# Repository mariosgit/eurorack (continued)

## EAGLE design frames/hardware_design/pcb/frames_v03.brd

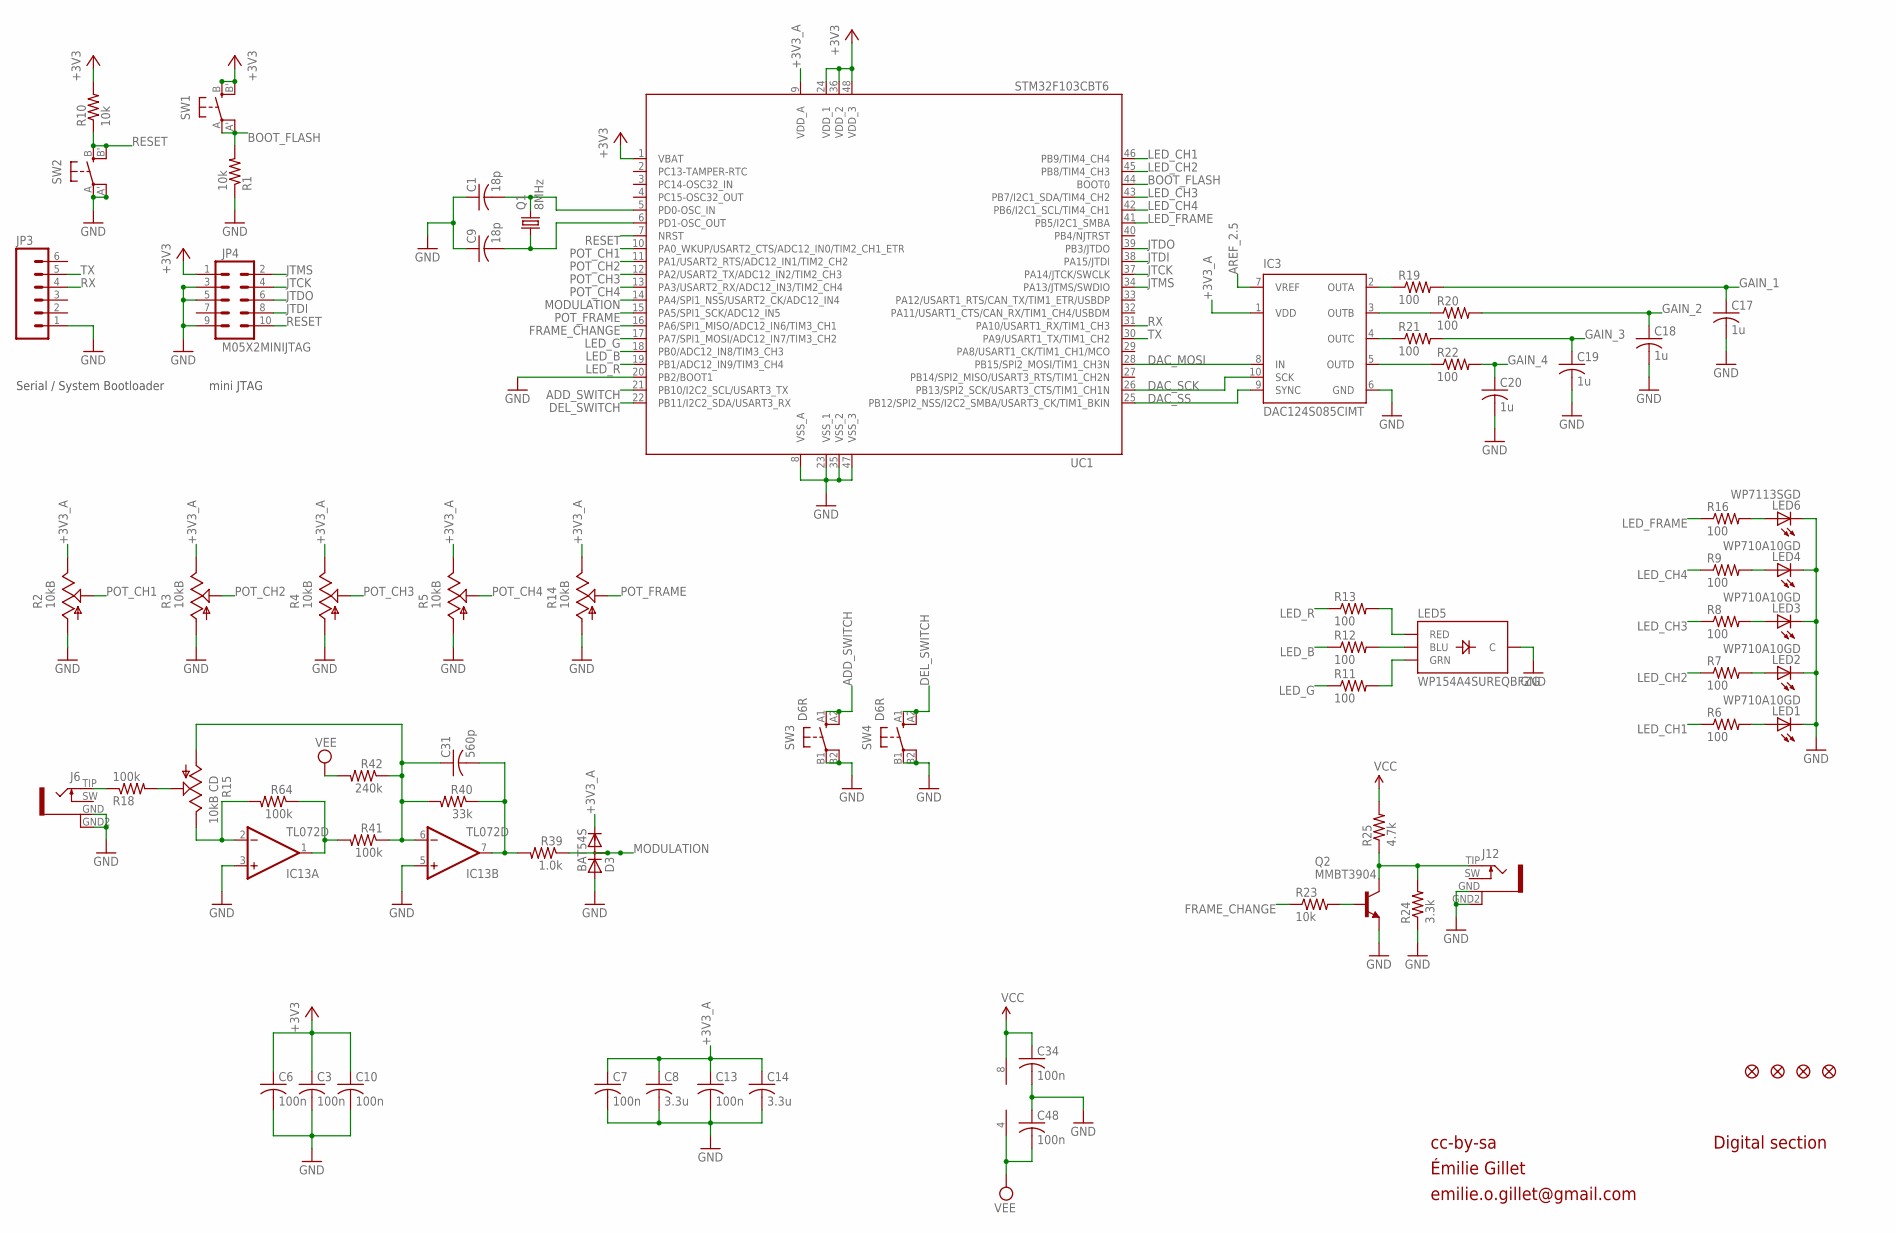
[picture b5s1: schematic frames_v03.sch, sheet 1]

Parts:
C1, C9: 18p; C0603
C3, C6, C7, C10, C13, C34, C48: 100n; C0603
C8, C14: 3.3u; C0603
C17, C18, C19, C20: 1u; C0603
C31: 560p; C0603
D3: BAT54S; SOT23
F1, F2, F3, F4: FIDUCIAL1X2; FIDUCIAL-1X2
IC3: DAC124S085CIMT; MSOP10
IC13: TL072D; SO08
J6, J12: PJ301WQP; WQP_PJ_301BM
JP3: M06SIP; 1X06
JP4: M05X2MINIJTAG; 2X5-1.27
LED1, LED2, LED3, LED4: WP710A10GD; LED3MM
LED5: WP154A4SUREQBFZG; LED-TRICOLOR-THROUGHHOLE
LED6: WP7113SGD; LED5MM
Q1: 8MHz; HC49UP
Q2: MMBT3904; SOT23-BEC
R1, R10, R23: 10k; R0603
R2, R3, R4, R5, R14: 10kB; ALPS_POT_VERTICAL_PS
R6, R7, R8, R9, R11, R12, R13, R16, R19, R20, R21, R22: 100; R0603
R15: 10kB CD; ALPS_POT_VERTICAL_PS
R18, R41, R64: 100k; R0603
R24: 3.3k; R0603
R25: 4.7k; R0603
R39: 1.0k; R0603
R40: 33k; R0603
R42: 240k; R0603
SW1, SW2: EVQQ2; EVQ-Q2
SW3, SW4: D6R
UC1: STM32F103CBT6; LQFP48

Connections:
+3V3: C3.1, C6.1, C10.1, JP4.1, R10.2, SW1.B (S), SW1.B' (S1), UC1.1 (VBAT), UC1.24 (VDD_1), UC1.36 (VDD_2), UC1.48 (VDD_3); also elsewhere on the board
+3V3_A: C7.1, C8.1, C13.1, C14.1, D3.2 (C), IC3.1 (VDD), R2.P$1 (E), R3.P$1 (E), R4.P$1 (E), R5.P$1 (E), R14.P$1 (E), UC1.9 (VDD_A); also elsewhere on the board
ADD_SWITCH: SW3.A1 (S), SW3.A2 (S1), UC1.21 (PB10/I2C2_SCL/USART3_TX)
AREF_2.5: IC3.7 (VREF); also elsewhere on the board
BOOT_FLASH: R1.2, SW1.A, SW1.A' (P1), UC1.44 (BOOT0)
DAC_MOSI: IC3.8 (IN), UC1.28 (PB15/SPI2_MOSI/TIM1_CH3N)
DAC_SCK: IC3.10 (SCK), UC1.26 (PB13/SPI2_SCK/USART3_CTS/TIM1_CH1N)
DAC_SS: IC3.9 (SYNC), UC1.25 (PB12/SPI2_NSS/I2C2_SMBA/USART3_CK/TIM1_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)
DEL_SWITCH: SW4.A1 (S), SW4.A2 (S1), UC1.22 (PB11/I2C2_SDA/USART3_RX)
FRAME_CHANGE: R23.1, UC1.16 (PA6/SPI1_MISO/ADC12_IN6/TIM3_CH1)
GAIN_1: C17.1, R19.2; also elsewhere on the board
GAIN_2: C18.1, R20.2; also elsewhere on the board
GAIN_3: C19.1, R21.2; also elsewhere on the board
GAIN_4: C20.1, R22.2; also elsewhere on the board
GATE2_LED: LED3.A, R8.2
GATE3_LED: LED2.A, R7.2
GATE4_LED: LED1.A, R6.2
GND: C1.1, C3.2, C6.2, C7.2, C8.2, C9.1, C10.2, C13.2, C14.2, C17.2, C18.2, C19.2, C20.2, C34.2, C48.1, D3.1 (A), IC3.6 (GND), IC13.3 (+IN), IC13.5 (+IN), J6.GND (1), J6.GND2 (4), J12.GND (1), J12.GND2 (4), JP3.1, JP4.3, JP4.5, JP4.9, LED1.K (C), LED2.K (C), LED3.K (C), LED4.K (C), LED5.GND (C), LED6.K (C), Q2.E, R1.1, R2.P$3 (A), R3.P$3 (A), R4.P$3 (A), R5.P$3 (A), R14.P$3 (A), R24.1, SW2.A, SW2.A' (P1), SW3.B1, SW3.B2 (P1), SW4.B1, SW4.B2 (P1), UC1.8 (VSS_A), UC1.20 (PB2/BOOT1), UC1.23 (VSS_1), UC1.35 (VSS_2), UC1.47 (VSS_3); also elsewhere on the board
JTCK: JP4.4, UC1.37 (PA14/JTCK/SWCLK)
JTDI: JP4.8, UC1.38 (PA15/JTDI)
JTDO: JP4.6, UC1.39 (PB3/JTDO)
JTMS: JP4.2, UC1.34 (PA13/JTMS/SWDIO)
LED_B: R12.1, UC1.18 (PB0/ADC12_IN8/TIM3_CH3)
LED_CH1: R6.1, UC1.46 (PB9/TIM4_CH4)
LED_CH2: R7.1, UC1.45 (PB8/TIM4_CH3)
LED_CH3: R8.1, UC1.43 (PB7/I2C1_SDA/TIM4_CH2)
LED_CH4: R9.1, UC1.42 (PB6/I2C1_SCL/TIM4_CH1)
LED_FRAME: R16.1, UC1.41 (PB5/I2C1_SMBA)
LED_G: R11.1, UC1.17 (PA7/SPI1_MOSI/ADC12_IN7/TIM3_CH2)
LED_R: R13.1, UC1.19 (PB1/ADC12_IN9/TIM3_CH4)
MODULATION: D3.3 (AC), R39.1, UC1.14 (PA4/SPI1_NSS/USART2_CK/ADC12_IN4)
unnamed: IC13.2 (-IN), R15.P$1 (E), R64.2
unnamed: R15.P$2 (S), R18.2
unnamed: LED4.A, R9.2
unnamed: C1.2, Q1.2, UC1.5 (PD0-OSC_IN)
unnamed: C9.2, Q1.1, UC1.6 (PD1-OSC_OUT)
unnamed: IC13.1 (OUT), R41.2, R64.1
unnamed: J6.TIP (2), R18.1
unnamed: C31.2, IC13.7 (OUT), R39.2, R40.1
unnamed: C31.1, IC13.6 (-IN), R15.P$3 (A), R40.2, R41.1, R42.1
unnamed: LED6.A, R16.2
unnamed: LED5.RED, R13.2
unnamed: LED5.BLU, R12.2
unnamed: LED5.GRN, R11.2
unnamed: IC3.2 (OUTA), R19.1
unnamed: IC3.3 (OUTB), R20.1
unnamed: IC3.4 (OUTC), R21.1
unnamed: J12.TIP (2), Q2.C, R24.2, R25.1
unnamed: IC3.5 (OUTD), R22.1
unnamed: Q2.B, R23.2
POT_CH1: R2.P$2 (S), UC1.10 (PA0_WKUP/USART2_CTS/ADC12_IN0/TIM2_CH1_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)
POT_CH2: R3.P$2 (S), UC1.11 (PA1/USART2_RTS/ADC12_IN1/TIM2_CH2)
POT_CH3: R4.P$2 (S), UC1.12 (PA2/USART2_TX/ADC12_IN2/TIM2_CH3)
POT_CH4: R5.P$2 (S), UC1.13 (PA3/USART2_RX/ADC12_IN3/TIM2_CH4)
POT_FRAME: R14.P$2 (S), UC1.15 (PA5/SPI1_SCK/ADC12_IN5)
RESET: JP4.10, R10.1, SW2.B (S), SW2.B' (S1), UC1.7 (NRST)
RX: JP3.4, UC1.31 (PA10/USART1_RX/TIM1_CH3)
TX: JP3.5, UC1.30 (PA9/USART1_TX/TIM1_CH2)
VCC: C34.1, IC13.8 (V+), R25.2; also elsewhere on the board
VEE: C48.2, IC13.4 (V-), R42.2; also elsewhere on the board

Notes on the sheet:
cc-by-sa
Serial / System Bootloader
mini JTAG
Digital section
Émilie Gillet
emilie.o.gillet@gmail.com

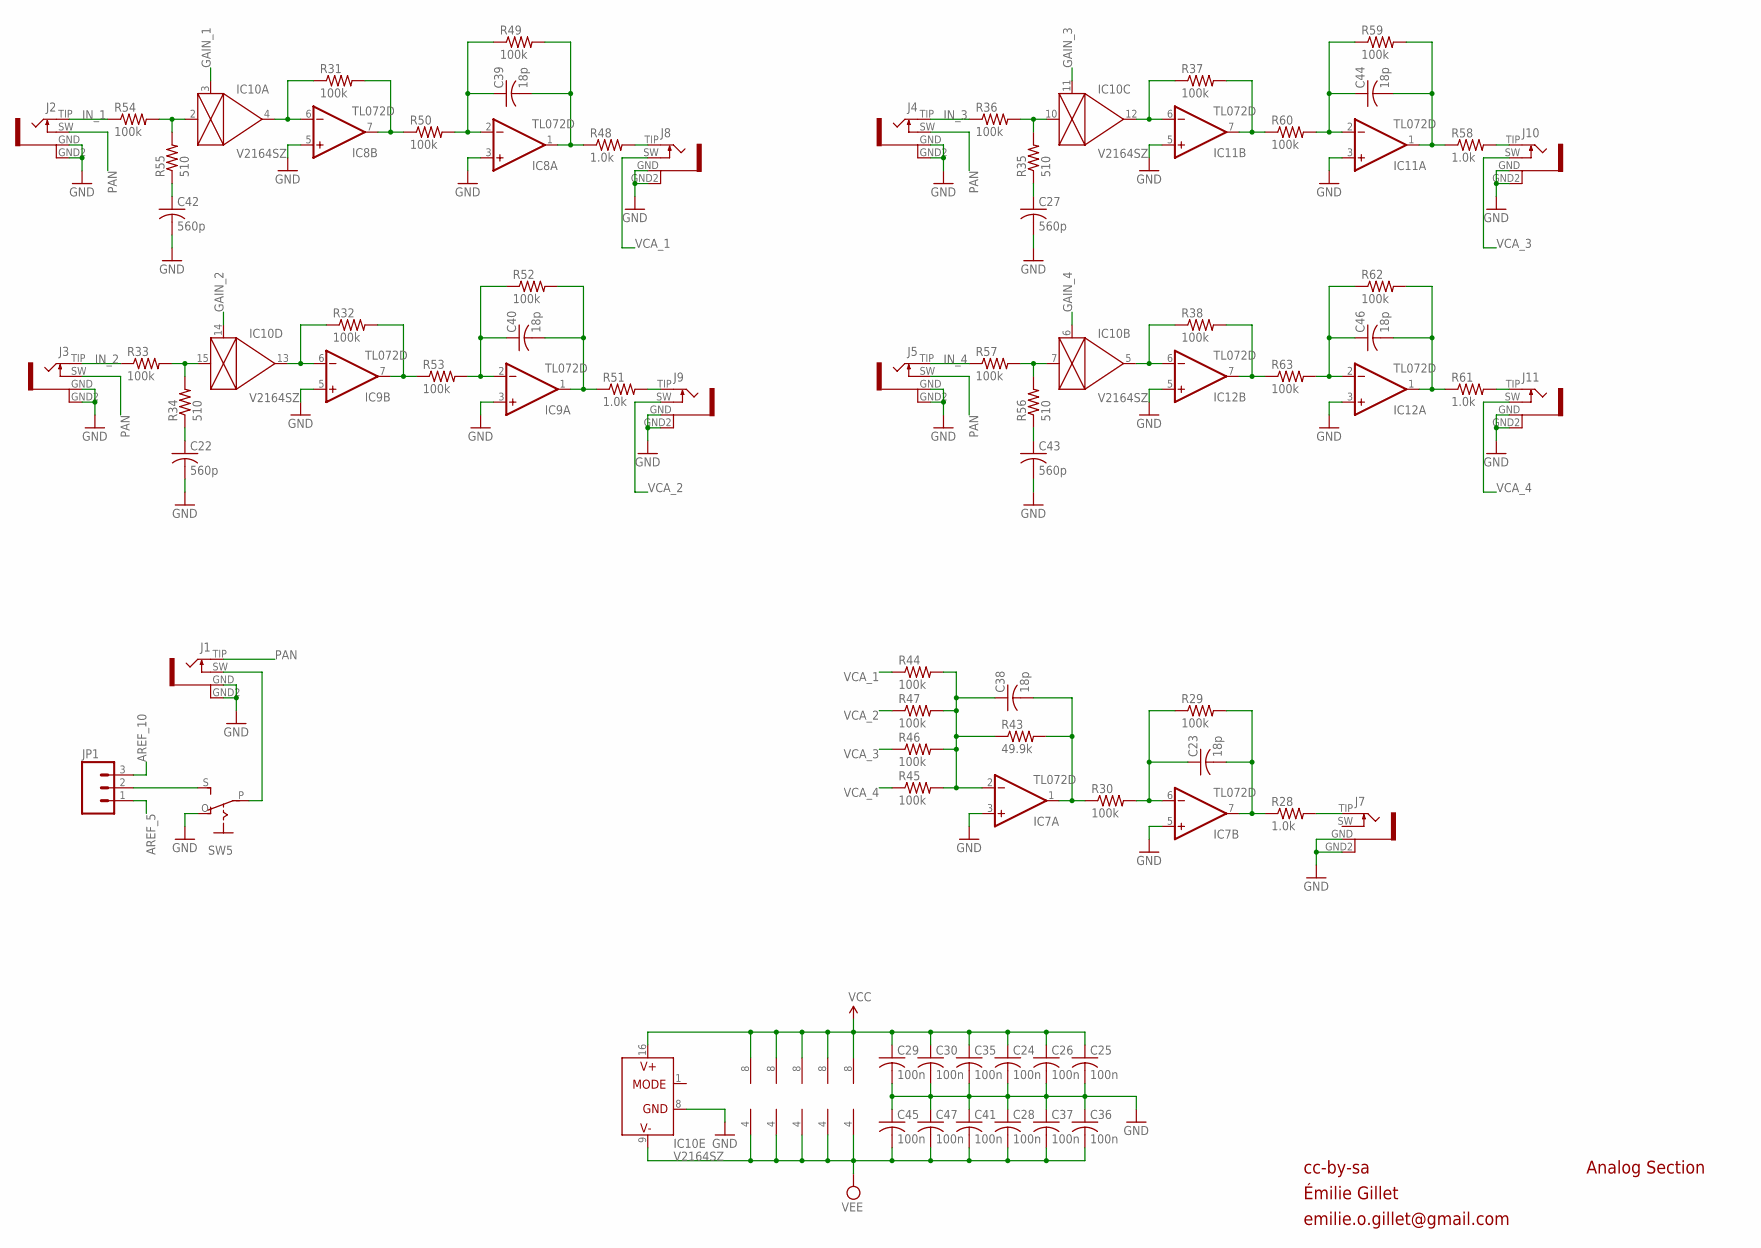
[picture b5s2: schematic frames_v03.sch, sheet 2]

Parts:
C22, C27, C42, C43: 560p; C0603
C23, C38, C39, C40, C44, C46: 18p; C0603
C24, C25, C26, C28, C29, C30, C35, C36, C37, C41, C45, C47: 100n; C0603
IC7, IC8, IC9, IC11, IC12: TL072D; SO08
IC10: V2164SZ; SOIC16N
J1, J2, J3, J4, J5, J7, J8, J9, J10, J11: PJ301WQP; WQP_PJ_301BM
JP1: M03PTH; 1X03
R28, R48, R51, R58, R61: 1.0k; R0603
R29, R30, R31, R32, R33, R36, R37, R38, R44, R45, R46, R47, R49, R50, R52, R53, R54, R57, R59, R60, R62, R63: 100k; R0603
R34, R35, R55, R56: 510; R0603
R43: 49.9k; R0603
SW5: S-ON-ONSMALL_SLIDE; ES_100SP1T6B11M2QEH_SMALL

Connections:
AREF_5: JP1.1; also elsewhere on the board
AREF_10: JP1.3; also elsewhere on the board
FB_CURRENT: IC10.2 (IN), R54.2, R55.2
FB_CURRENT1: IC10.15 (IN), R33.2, R34.2
FB_CURRENT2: IC10.10 (IN), R35.2, R36.2
FB_CURRENT3: IC10.7 (IN), R56.2, R57.2
GAIN_1: IC10.3 (CTRL); also elsewhere on the board
GAIN_2: IC10.14 (CTRL); also elsewhere on the board
GAIN_3: IC10.11 (CTRL); also elsewhere on the board
GAIN_4: IC10.6 (CTRL); also elsewhere on the board
GND: C22.2, C24.2, C25.2, C26.2, C27.2, C28.1, C29.2, C30.2, C35.2, C36.1, C37.1, C41.1, C42.2, C43.2, C45.1, C47.1, IC7.3 (+IN), IC7.5 (+IN), IC8.3 (+IN), IC8.5 (+IN), IC9.3 (+IN), IC9.5 (+IN), IC10.8 (GND), IC11.3 (+IN), IC11.5 (+IN), IC12.3 (+IN), IC12.5 (+IN), J1.GND (1), J1.GND2 (4), J2.GND (1), J2.GND2 (4), J3.GND (1), J3.GND2 (4), J4.GND (1), J4.GND2 (4), J5.GND (1), J5.GND2 (4), J7.GND (1), J7.GND2 (4), J8.GND (1), J8.GND2 (4), J9.GND (1), J9.GND2 (4), J10.GND (1), J10.GND2 (4), J11.GND (1), J11.GND2 (4), SW5.O; also elsewhere on the board
IN_1: J2.TIP (2), R54.1
IN_2: J3.TIP (2), R33.1
IN_3: J4.TIP (2), R36.1
IN_4: J5.TIP (2), R57.1
unnamed: C42.1, R55.1
unnamed: J7.TIP (2), R28.2
unnamed: IC9.7 (OUT), R32.2, R53.1
unnamed: C27.1, R35.1
unnamed: IC8.6 (-IN), IC10.4 (OUT), R31.1
unnamed: C39.1, IC8.2 (-IN), R49.1, R50.2
unnamed: C39.2, IC8.1 (OUT), R48.1, R49.2
unnamed: C23.2, IC7.7 (OUT), R28.1, R29.2
unnamed: C22.1, R34.1
unnamed: C38.1, IC7.2 (-IN), R43.1, R44.2, R45.2, R46.2, R47.2
unnamed: IC9.6 (-IN), IC10.13 (OUT), R32.1
unnamed: C23.1, IC7.6 (-IN), R29.1, R30.2
unnamed: C40.1, IC9.2 (-IN), R52.1, R53.2
unnamed: C40.2, IC9.1 (OUT), R51.1, R52.2
unnamed: IC10.12 (OUT), IC11.6 (-IN), R37.1
unnamed: C44.1, IC11.2 (-IN), R59.1, R60.2
unnamed: C44.2, IC11.1 (OUT), R58.1, R59.2
unnamed: C43.1, R56.1
unnamed: C38.2, IC7.1 (OUT), R30.1, R43.2
unnamed: IC10.5 (OUT), IC12.6 (-IN), R38.1
unnamed: C46.1, IC12.2 (-IN), R62.1, R63.2
unnamed: C46.2, IC12.1 (OUT), R61.1, R62.2
unnamed: J1.SW (3), SW5.P
unnamed: J8.TIP (2), R48.2
unnamed: JP1.2, SW5.S
unnamed: IC12.7 (OUT), R38.2, R63.1
unnamed: J9.TIP (2), R51.2
unnamed: J11.TIP (2), R61.2
unnamed: J10.TIP (2), R58.2
PAN: J1.TIP (2), J2.SW (3), J3.SW (3), J4.SW (3), J5.SW (3)
VCA0_1: IC8.7 (OUT), R31.2, R50.1
VCA0_3: IC11.7 (OUT), R37.2, R60.1
VCA_1: J8.SW (3), R44.1
VCA_2: J9.SW (3), R47.1
VCA_3: J10.SW (3), R46.1
VCA_4: J11.SW (3), R45.1
VCC: C24.1, C25.1, C26.1, C29.1, C30.1, C35.1, IC7.8 (V+), IC8.8 (V+), IC9.8 (V+), IC10.16 (V+), IC11.8 (V+), IC12.8 (V+); also elsewhere on the board
VEE: C28.2, C36.2, C37.2, C41.2, C45.2, C47.2, IC7.4 (V-), IC8.4 (V-), IC9.4 (V-), IC10.9 (V-), IC11.4 (V-), IC12.4 (V-); also elsewhere on the board

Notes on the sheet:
cc-by-sa
Analog Section
Émilie Gillet
emilie.o.gillet@gmail.com

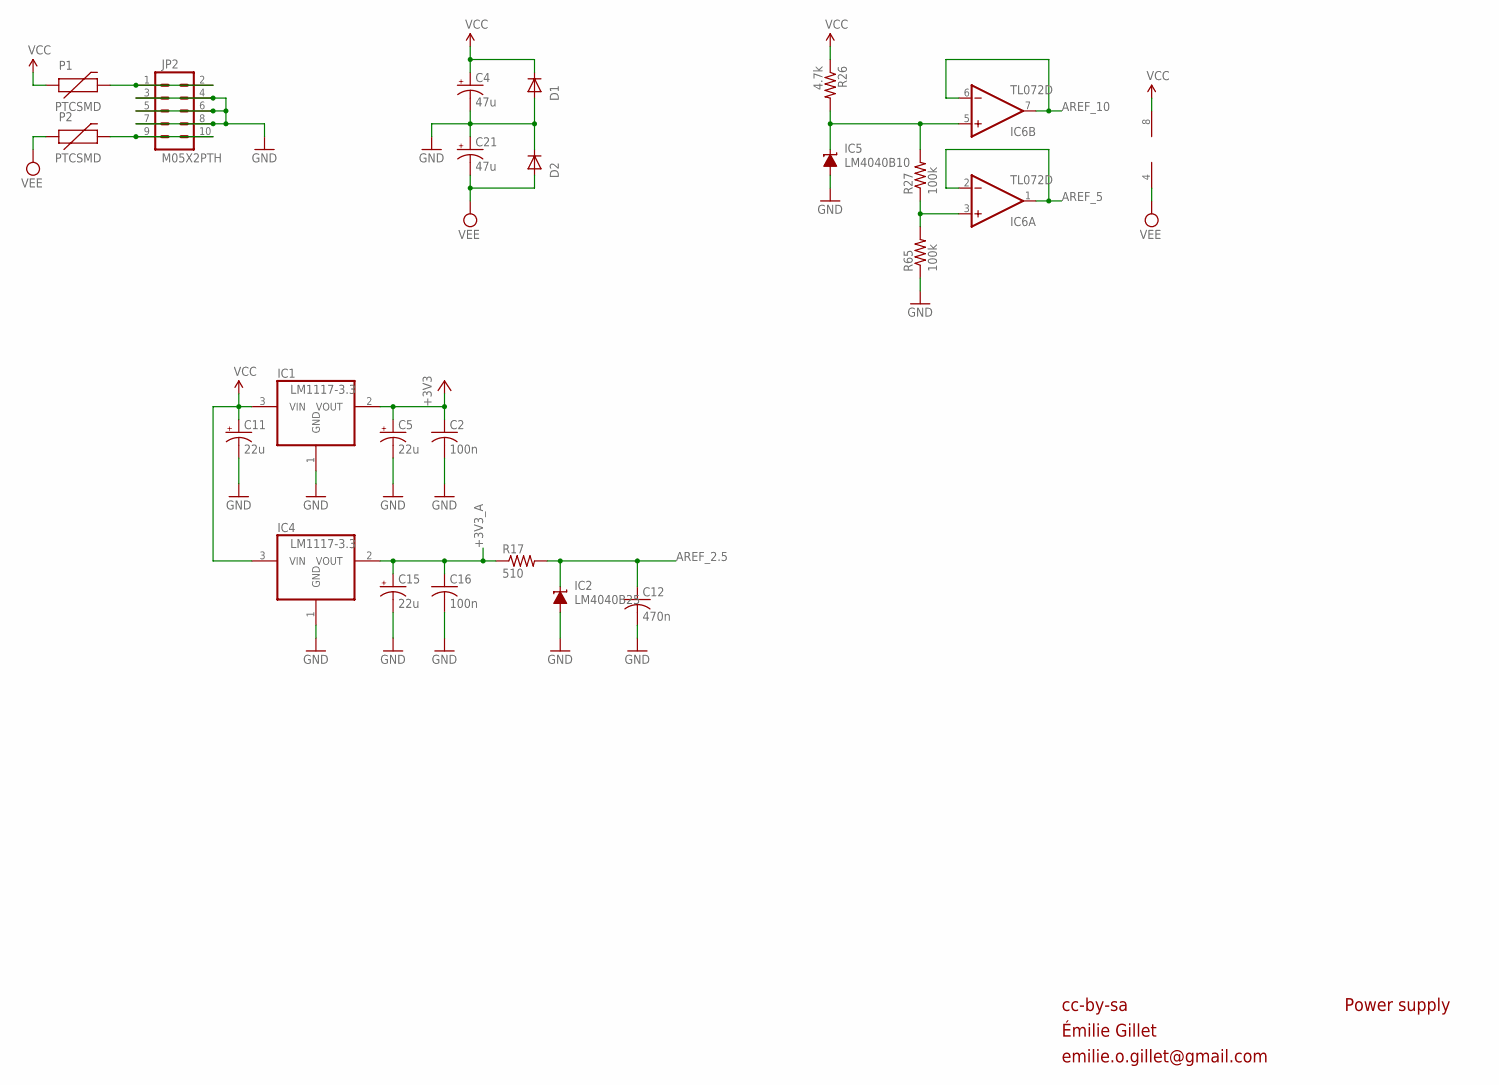
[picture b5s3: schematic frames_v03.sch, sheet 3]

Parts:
C2, C16: 100n; C0603
C4, C21: 47u; PANASONIC_D
C5, C11, C15: 22u; PANASONIC_C
C12: 470n; C0603
D1, D2: 1N5819HW; SOD123
IC1, IC4: LM1117-3.3; SOT223
IC2: LM4040B25; DBZ_R-PDSO-G3
IC5: LM4040B10; DBZ_R-PDSO-G3
IC6: TL072D; SO08
JP2: M05X2PTH; AVR_ICSP
P1, P2: PTCSMD; PTC-1206
R17: 510; R0603
R26: 4.7k; R0603
R27, R65: 100k; R0603

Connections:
+3V3: C2.1, C5.+, IC1.2 (VOUT); also elsewhere on the board
+3V3_A: C15.+, C16.1, IC4.2 (VOUT), R17.1; also elsewhere on the board
AREF_2.5: C12.1, IC2.1 (C), R17.2; also elsewhere on the board
AREF_5: IC6.1 (OUT), IC6.2 (-IN); also elsewhere on the board
AREF_10: IC6.6 (-IN), IC6.7 (OUT); also elsewhere on the board
AREF_10_0: IC5.1 (C), IC6.5 (+IN), R26.2, R27.2
GND: C2.2, C4.-, C5.-, C11.-, C12.2, C15.-, C16.2, C21.+, D1.A, D2.C, IC1.1 (GND), IC2.2 (A), IC4.1 (GND), IC5.2 (A), JP2.3, JP2.4, JP2.5, JP2.6, JP2.7, JP2.8, R65.1; also elsewhere on the board
unnamed: IC6.3 (+IN), R27.1, R65.2
unnamed: JP2.1, JP2.2, P1.2
unnamed: JP2.9, JP2.10, P2.2
VCC: C4.+, C11.+, D1.C, IC1.3 (VIN), IC4.3 (VIN), IC6.8 (V+), P1.1, R26.1; also elsewhere on the board
VEE: C21.-, D2.A, IC6.4 (V-), P2.1; also elsewhere on the board

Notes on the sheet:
cc-by-sa
Power supply
Émilie Gillet
emilie.o.gillet@gmail.com

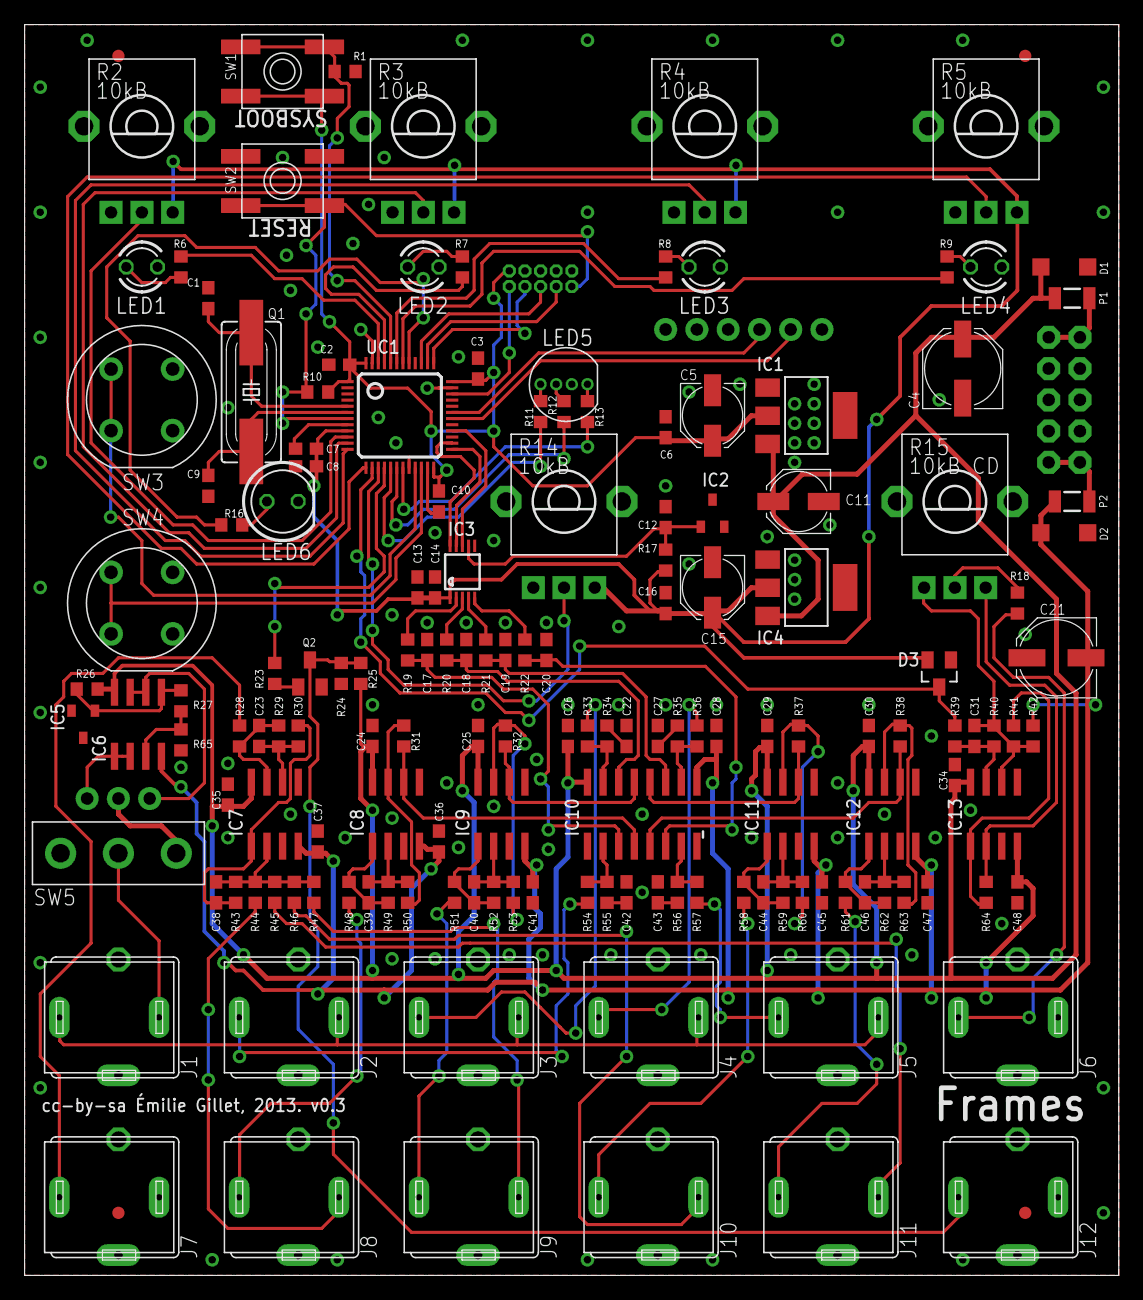
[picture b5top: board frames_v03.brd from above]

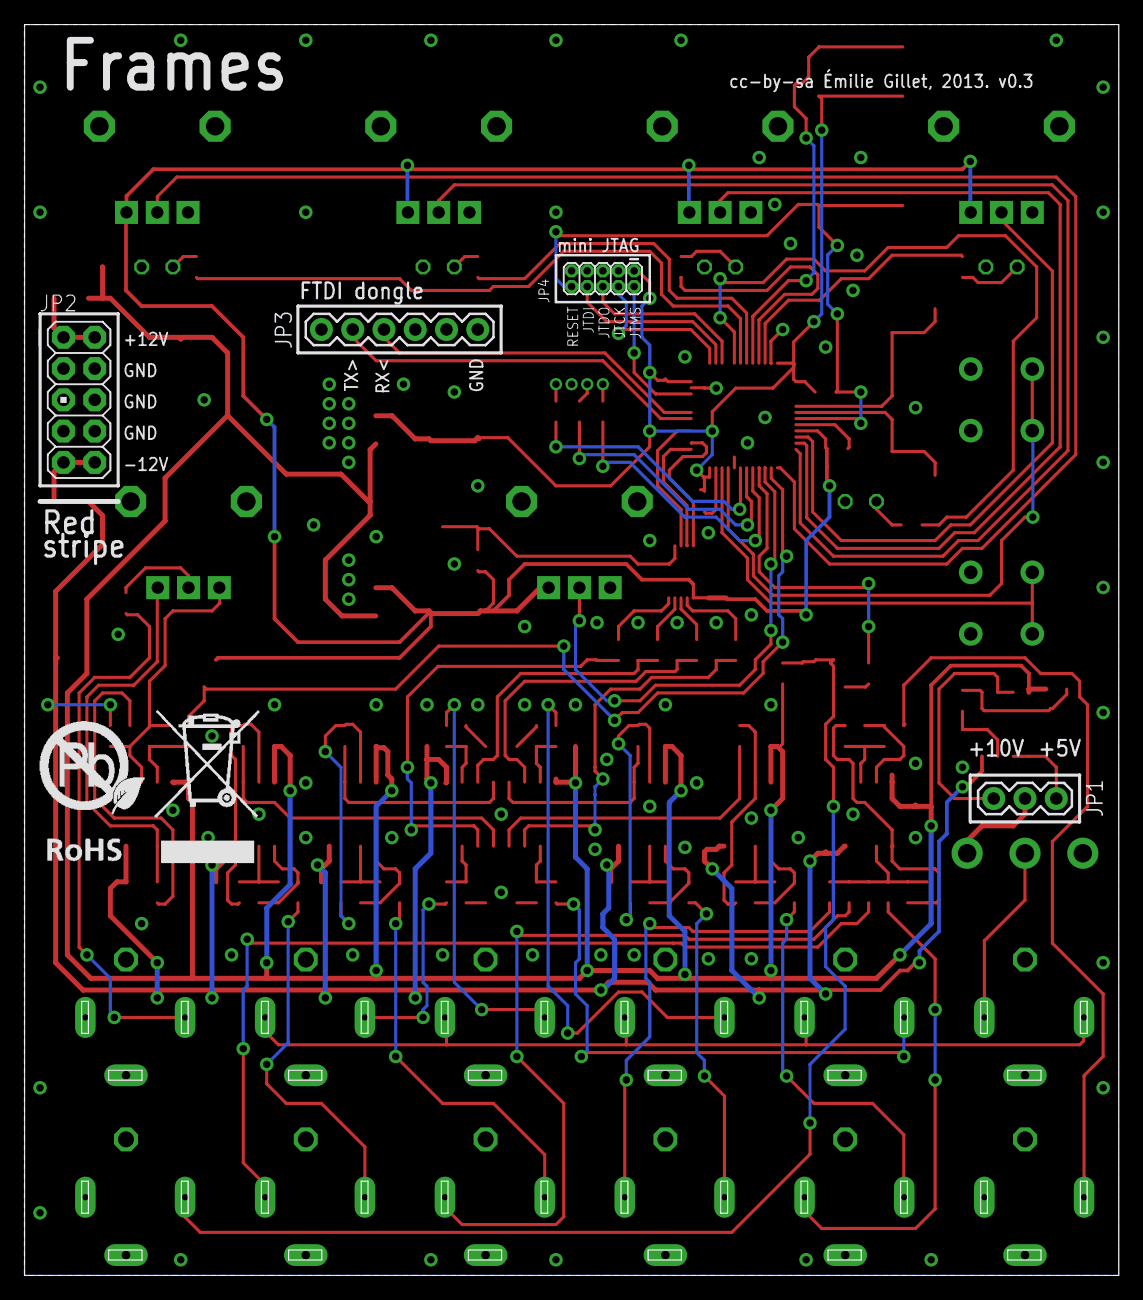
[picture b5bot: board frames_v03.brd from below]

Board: 2 copper layers, 88.9 x 101.6 mm, 165 parts (5 on the bottom side), 110 nets.

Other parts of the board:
U$1: EURORACK_TEMPLATE
U$3: ROHS_BIG

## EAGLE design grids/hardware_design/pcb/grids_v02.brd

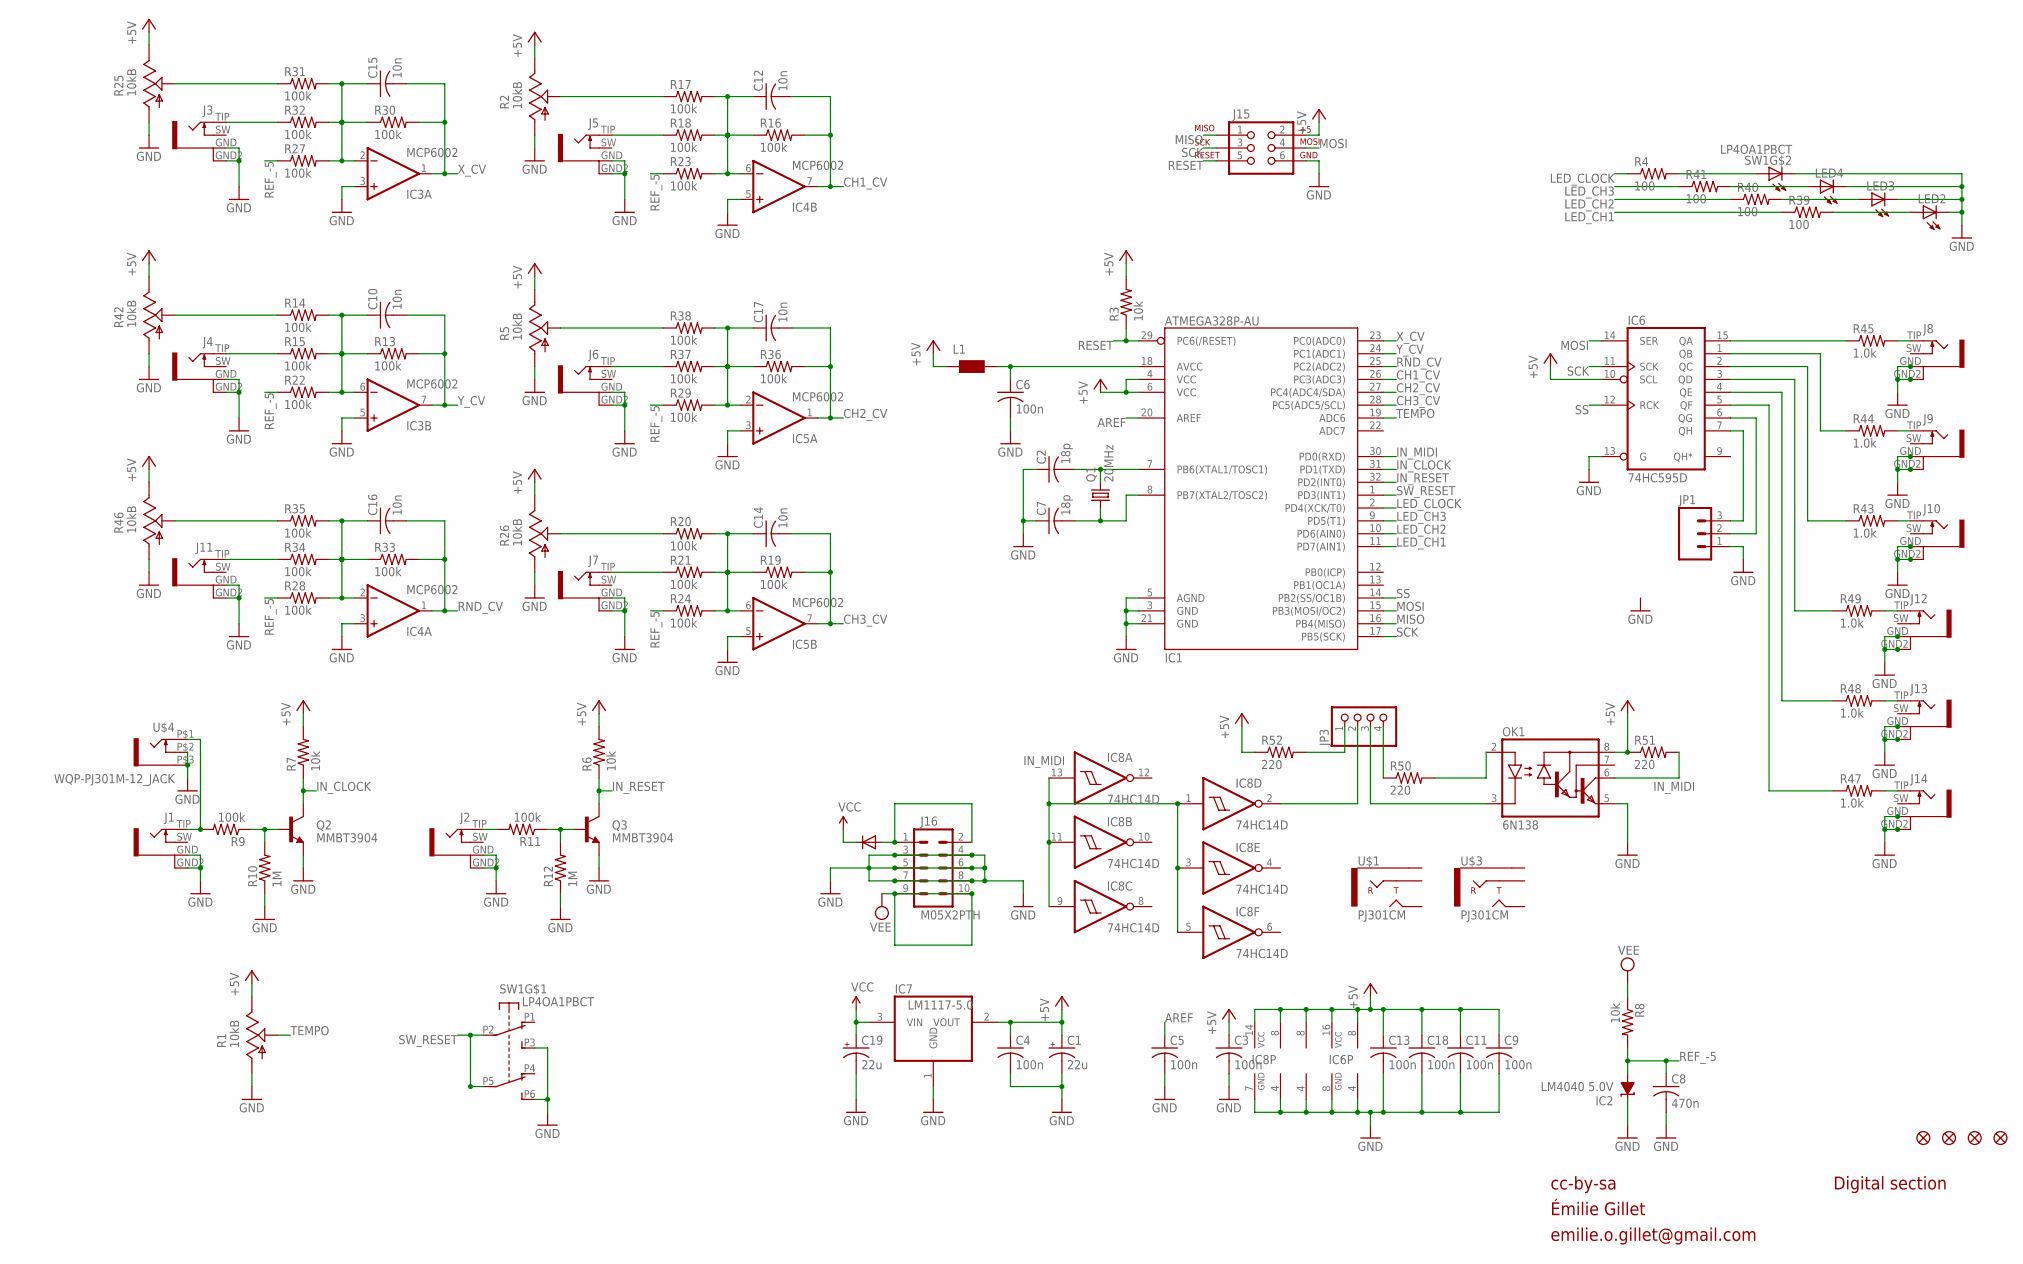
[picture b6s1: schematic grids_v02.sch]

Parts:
C1, C19: 22u; PANASONIC_C
C2, C7: 18p; C0603
C3, C4, C5, C6, C9, C11, C13, C18: 100n; C0603
C8: 470n; C0603
C10, C12, C14, C15, C16, C17: 10n; C0603
D1: 1N5819HW; SOD123
F1, F2, F3, F4: FIDUCIAL1X2; FIDUCIAL-1X2
IC1: ATMEGA328P-AU; TQFP32-08
IC2: LM4040 5.0V; DBZ_R-PDSO-G3
IC3, IC4, IC5: MCP6002; SO08
IC6: 74HC595D; SO16
IC7: LM1117-5.0; SOT223
IC8: 74HC14D; SO14
J1, J2, J3, J4, J5, J6, J7, J8, J9, J10, J11, J12, J13, J14: PJ301WQP; WQP_PJ_301BM
J15: AVR_SPI_PRG_6PTH; 2X3
J16: M05X2PTH; AVR_ICSP
JP1: M03PTH; 1X03
JP3: PINHD-1X4; 1X04
L1: WE-CBF_0603; 0603
LED2, LED3, LED4: LED3MM
OK1: 6N138; DIL08
Q1: 20MHz; HC49UP
Q2, Q3: MMBT3904; SOT23-BEC
R1, R2, R5, R25, R26, R46: 10kB; ALPS_POT_VERTICAL_PS
R3, R6, R7, R8: 10k; R0603
R4, R39, R40, R41: 100; R0603
R9, R11, R13, R14, R15, R16, R17, R18, R19, R20, R21, R22, R23, R24, R27, R28, R29, R30, R31, R32, R33, R34, R35, R36, R37, R38: 100k; R0603
R10, R12: 1M; R0603
R42: 10kB; ALPS_POT_VERTICAL_PS4
R43, R44, R45, R47, R48, R49: 1.0k; R0603
R50, R51, R52: 220; R0603
SW1: LP4OA1PBCT
U$1, U$3: PJ301CM
U$4: WQP-PJ301M-12_JACK

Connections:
+5V: C1.+, C3.1, C4.1, C9.1, C11.1, C13.1, C18.1, IC1.4 (VCC), IC1.6 (VCC), IC3.8 (V+), IC4.8 (V+), IC5.8 (V+), IC6.10 (SCL), IC6.16 (VCC), IC7.2 (VOUT), IC8.14 (VCC), J15.2, L1.1, OK1.8 (VCC), R1.P$1 (E), R2.P$1 (E), R3.2, R5.P$1 (E), R6.2, R7.2, R25.P$1 (E), R26.P$1 (E), R42.P$1 (E), R46.P$1 (E), R51.1, R52.1
AREF: C5.1, IC1.20 (AREF)
CH1_CV: C12.2, IC1.26 (PC3(ADC3)), IC4.7 (OUT), R16.2
CH2_CV: C17.2, IC1.27 (PC4(ADC4/SDA)), IC5.1 (OUT), R36.2
CH3_CV: C14.2, IC1.28 (PC5(ADC5/SCL)), IC5.7 (OUT), R19.2
CLOCK_OUT: IC6.6 (QG), JP1.2
GATE1_IN: J1.TIP (2), R9.2, U$4.P$1 (2)
GATE1_LED: R4.2, SW1.L1
GATE2_IN: J2.TIP (2), R11.2
GATE2_LED: LED4.A, R41.2
GATE3_LED: LED3.A, R40.2
GATE4_LED: LED2.A, R39.2
GND: C1.-, C2.1, C3.2, C4.2, C5.2, C6.2, C7.1, C8.2, C9.2, C11.2, C13.2, C18.2, C19.-, IC1.3 (GND), IC1.5 (AGND), IC1.21 (GND), IC2.1 (C), IC3.3 (+IN), IC3.4 (V-), IC3.5 (+IN), IC4.3 (+IN), IC4.4 (V-), IC4.5 (+IN), IC5.3 (+IN), IC5.4 (V-), IC5.5 (+IN), IC6.8 (GND), IC6.13 (G), IC7.1 (GND), IC8.7 (GND), J1.GND (1), J1.GND2 (4), J2.GND (1), J2.GND2 (4), J3.GND (1), J3.GND2 (4), J4.GND (1), J4.GND2 (4), J5.GND (1), J5.GND2 (4), J6.GND (1), J6.GND2 (4), J7.GND (1), J7.GND2 (4), J8.GND (1), J8.GND2 (4), J9.GND (1), J9.GND2 (4), J10.GND (1), J10.GND2 (4), J11.GND (1), J11.GND2 (4), J12.GND (1), J12.GND2 (4), J13.GND (1), J13.GND2 (4), J14.GND (1), J14.GND2 (4), J15.6, J16.3, J16.4, J16.5, J16.6, J16.7, J16.8, JP1.1, LED2.K (C), LED3.K (C), LED4.K (C), OK1.5 (GND), Q2.E, Q3.E, R1.P$3 (A), R2.P$3 (A), R5.P$3 (A), R10.1, R12.1, R25.P$3 (A), R26.P$3 (A), R42.P$3 (A), R46.P$3 (A), SW1.L2, SW1.P3 (A3), SW1.P6 (B3), U$4.P$2 (3), U$4.P$3 (1)
IN_CLOCK: IC1.31 (PD1(TXD)), Q2.C, R7.1
IN_MIDI: IC1.30 (PD0(RXD)), IC8.1 (I), IC8.3 (I), IC8.5 (I), IC8.9 (I), IC8.11 (I), IC8.13 (I), OK1.6 (VO), R51.2
IN_RESET: IC1.32 (PD2(INT0)), Q3.C, R6.1
LED_CH1: IC1.11 (PD7(AIN1)), R39.1
LED_CH2: IC1.10 (PD6(AIN0)), R40.1
LED_CH3: IC1.9 (PD5(T1)), R41.1
LED_CLOCK: IC1.2 (PD4(XCK/T0)), R4.1
MISO: IC1.16 (PB4(MISO)), J15.1
MOSI: IC1.15 (PB3(MOSI/OC2)), IC6.14 (SER), J15.4
unnamed: Q2.B, R9.1, R10.2
unnamed: Q3.B, R11.1, R12.2
unnamed: D1.A, J16.1, J16.2
unnamed: J14.TIP (2), R47.2
unnamed: J13.TIP (2), R48.2
unnamed: J12.TIP (2), R49.2
unnamed: R25.P$2 (S), R31.1
unnamed: J3.TIP (2), R32.1
unnamed: C10.1, IC3.6 (-IN), R13.1, R14.2, R15.2, R22.2
unnamed: R14.1, R42.P$2 (S)
unnamed: J4.TIP (2), R15.1
unnamed: C16.1, IC4.2 (-IN), R28.2, R33.1, R34.2, R35.2
unnamed: R35.1, R46.P$2 (S)
unnamed: J11.TIP (2), R34.1
unnamed: C12.1, IC4.6 (-IN), R16.1, R17.2, R18.2, R23.2
unnamed: R2.P$2 (S), R17.1
unnamed: J5.TIP (2), R18.1
unnamed: C17.1, IC5.2 (-IN), R29.2, R36.1, R37.2, R38.2
unnamed: R5.P$2 (S), R38.1
unnamed: J6.TIP (2), R37.1
unnamed: C14.1, IC5.6 (-IN), R19.1, R20.2, R21.2, R24.2
unnamed: R20.1, R26.P$2 (S)
unnamed: J7.TIP (2), R21.1
unnamed: IC6.15 (QA), R45.1
unnamed: IC6.1 (QB), R44.1
unnamed: C15.1, IC3.2 (-IN), R27.2, R30.1, R31.2, R32.2
unnamed: IC6.2 (QC), R43.1
unnamed: IC6.3 (QD), R49.1
unnamed: IC6.4 (QE), R48.1
unnamed: IC6.5 (QF), R47.1
unnamed: J8.TIP (2), R45.2
unnamed: J9.TIP (2), R44.2
unnamed: J10.TIP (2), R43.2
unnamed: C6.1, IC1.18 (AVCC), L1.2
unnamed: JP3.1, R52.2
unnamed: IC8.2 (O), JP3.2
unnamed: OK1.2 (A), R50.2
unnamed: JP3.3, OK1.3 (C)
unnamed: JP3.4, R50.1
unnamed: C7.2, IC1.8 (PB7(XTAL2/TOSC2)), Q1.1
unnamed: C2.2, IC1.7 (PB6(XTAL1/TOSC1)), Q1.2
RANDOM_GATE: IC6.7 (QH), JP1.3
REF_-5: C8.1, IC2.2 (A), R8.2, R22.1, R23.1, R24.1, R27.1, R28.1, R29.1
RESET: IC1.29 (PC6(/RESET)), J15.5, R3.1
RND_CV: C16.2, IC1.25 (PC2(ADC2)), IC4.1 (OUT), R33.2
SCK: IC1.17 (PB5(SCK)), IC6.11 (SCK), J15.3
SS: IC1.14 (PB2(SS/OC1B)), IC6.12 (RCK)
SW_RESET: IC1.1 (PD3(INT1)), SW1.P2 (A2), SW1.P5 (B2)
TEMPO: IC1.19 (ADC6), R1.P$2 (S)
VCC: C19.+, D1.C, IC7.3 (VIN)
VEE: J16.9, J16.10, R8.1
X_CV: C15.2, IC1.23 (PC0(ADC0)), IC3.1 (OUT), R30.2
Y_CV: C10.2, IC1.24 (PC1(ADC1)), IC3.7 (OUT), R13.2

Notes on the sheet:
cc-by-sa
Digital section
Émilie Gillet
emilie.o.gillet@gmail.com
